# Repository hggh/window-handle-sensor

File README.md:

### window handle sensor

get the status of your windows. sensor is between your handle and the window.

### TODO

 * replace xc6220 footprint with the one from KiCAD
 * add a button for wifi reset
 * battery connector rotate it: open should be on top

### PCBs

this project contains of two pcbs.

#### window-handle-sensor

This PCB is the sensor. It has three hall sensors placed on a **0.6mm** pcb.

library used: https://github.com/hggh/kicad-libraries

##### BOM of window-handle-sensor pcb

| number | name |
|---| ---|
| C1,C2,C3 | ceramic cap 0.1 µF SMD 0805 |
| U1,U2,U3 | Infineon TLE4913 |

#### ESP controller board

This PCB is the controller board with the ESP32-S2. The thickness of this pcb can be 1.0-1.6mm.

##### BOM of esp32-s2 pcb

| number | name |
|--- | ---|
| C1 | ceramic cap 22µF SMD 0805 |
| C2 | ceramic cap 4.7µF SMD 0805 |
| C3 | tantalum cap 220µF SMD EIA-7343-31 |
| C4 | ceramic cap 100nF SMD 0805 |
| C5 | ceramic cap 1µF SMD 0805 |
| U1 | XC6220 3.0V SOT-25 |
| U2 | ESP32-S2-WROOM |
| H1 | 2.54mm 2x3 pin header |
| J1 | JST PH S2B-PH-K |
| Q1 | BC817 |
| Q2 | BC807 |
| R1, R14 | 10k SMD0805 |
| R2, R3, R4 | 100 SMD0805 |
| R5, R6, R7, R8, R9 | 10M SMD 0805 |
| R10, R11 | 1k1 SMD 0805 |
| R12, R13 | 10k SMD 0805 |

### case

The inlay is placed on the square bolt with 3x magnets.

Magnets: Ø 2 mm, h=1mm (strength: 110g): https://www.supermagnete.de/eng/disc-magnets-neodymium/disc-magnet-2mm-1mm_S-02-01-N

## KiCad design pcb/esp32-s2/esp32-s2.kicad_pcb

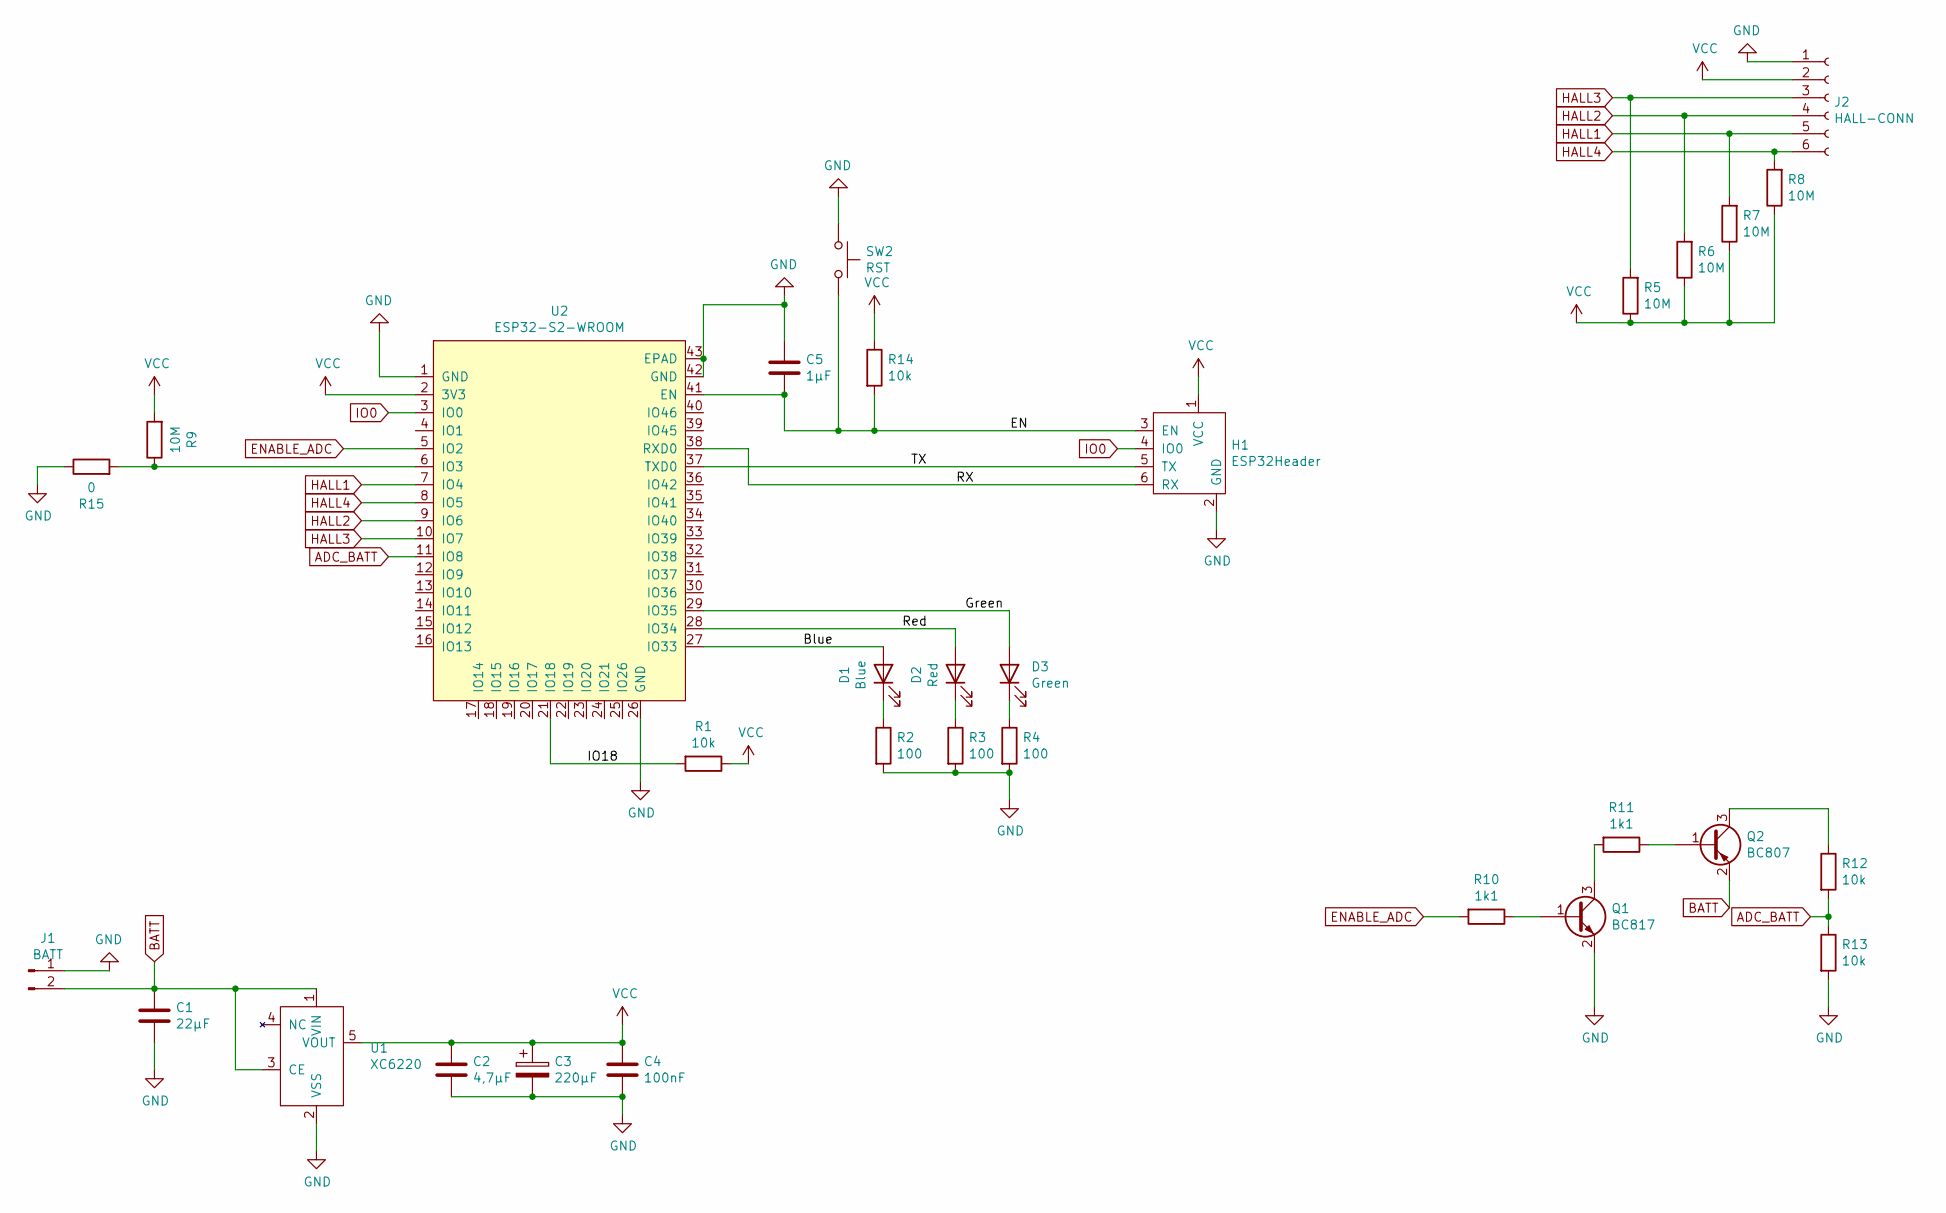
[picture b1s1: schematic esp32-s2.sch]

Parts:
C1: 22µF; C_0805_2012Metric
C2: 4,7µF; C_0805_2012Metric
C3: 220µF; CP_EIA-7343-31_Kemet-D
C4: 100nF; C_0805_2012Metric
C5: 1µF; C_0805_2012Metric
D1: Blue; LED_0805_2012Metric
D2: Red; LED_0805_2012Metric
D3: Green; LED_0805_2012Metric
H1: ESP32Header; esp32-prog-header
J1: BATT; JST_PH_S2B-PH-K_1x02_P2.00mm_Horizontal
J2: HALL-CONN; PinHeader_1x06_P2.00mm_Vertical
Q1: BC817; SOT-23
Q2: BC807; SOT-23
R1, R12, R13: 10k; R_0805_2012Metric
R2, R3, R4: 100; R_0805_2012Metric
R5, R6, R7, R8, R9: 10M; R_0805_2012Metric
R10, R11: 1k1; R_0805_2012Metric
R14: 10k; C_0805_2012Metric
R15: 0; R_0805_2012Metric
SW2: RST; SMD_Button
U1: XC6220
U2: ESP32-S2-WROOM

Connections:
/Blue: D1.2 (A), U2.27 (IO33)
/EN: C5.2, H1.3 (EN), R14.2, SW2.2, U2.41 (EN)
/Green: D3.2 (A), U2.29 (IO35)
/IO18: R1.2, U2.21 (IO18)
/RX: H1.6 (RX), U2.38 (RXD0)
/Red: D2.2 (A), U2.28 (IO34)
/TX: H1.5 (TX), U2.37 (TXD0)
ADC_BATT: R12.2, R13.1, U2.11 (IO8)
BATT: C1.1, J1.2, Q2.2 (E), U1.1 (VIN), U1.3 (CE)
ENABLE_ADC: R10.2, U2.5 (IO2)
GND: C1.2, C2.2, C3.2, C4.2, C5.1, H1.2 (GND), J1.1, J2.1, Q1.2 (E), R2.2, R3.2, R4.2, R13.2, R15.1, SW2.1, U1.2 (VSS), U2.1 (GND), U2.26 (GND), U2.42 (GND), U2.43 (EPAD)
HALL1: J2.5, R7.2, U2.7 (IO4)
HALL2: J2.4, R6.2, U2.9 (IO6)
HALL3: J2.3, R5.2, U2.10 (IO7)
HALL4: J2.6, R8.2, U2.8 (IO5)
IO0: H1.4 (IO0), U2.3 (IO0)
unnamed: D1.1 (K), R2.1
unnamed: D2.1 (K), R3.1
unnamed: D3.1 (K), R4.1
unnamed: Q1.1 (B), R10.1
unnamed: Q1.3 (C), R11.2
unnamed: Q2.1 (B), R11.1
unnamed: Q2.3 (C), R12.1
unnamed: R9.1, R15.2, U2.6 (IO3)
VCC: C2.1, C3.1, C4.1, H1.1 (VCC), J2.2, R1.1, R5.1, R6.1, R7.1, R8.1, R9.2, R14.1, U1.5 (VOUT), U2.2 (3V3)

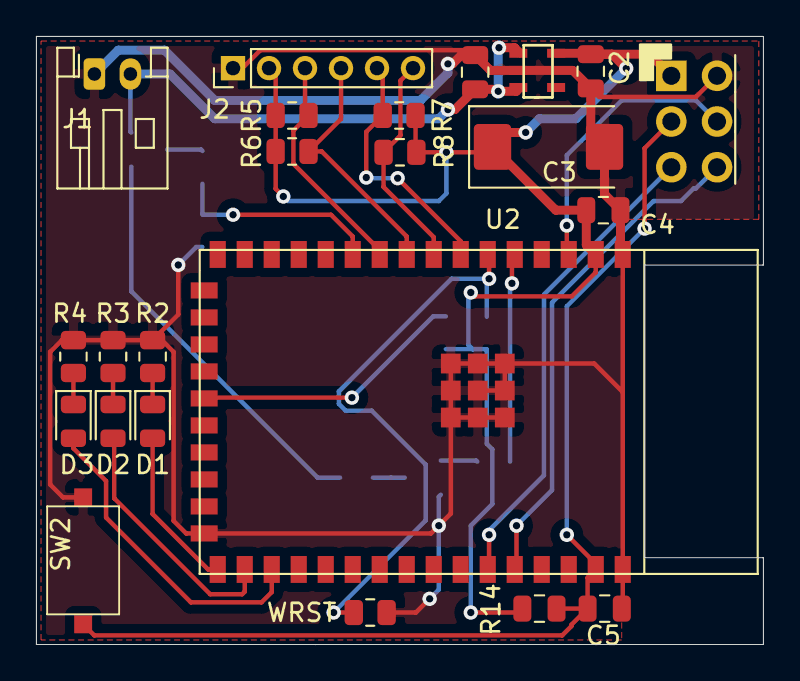
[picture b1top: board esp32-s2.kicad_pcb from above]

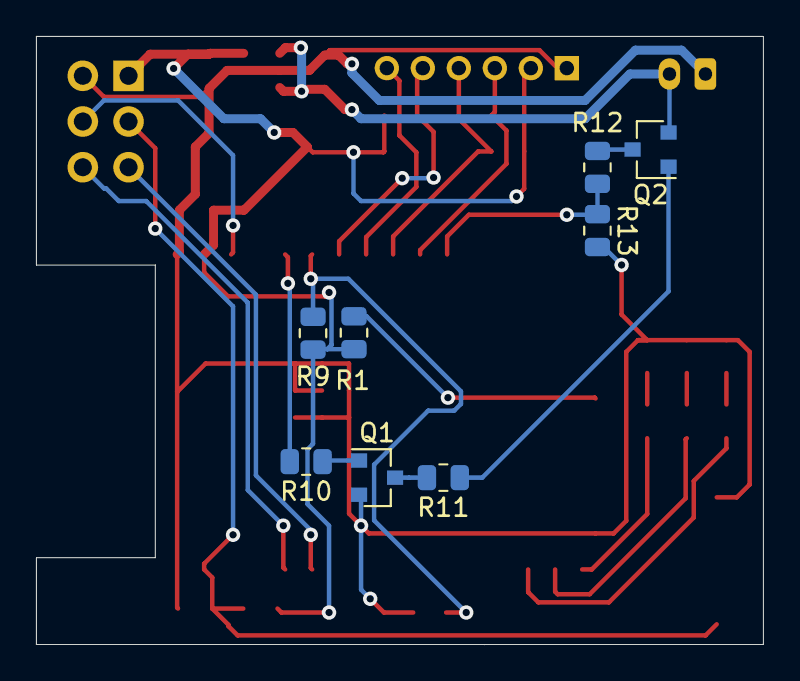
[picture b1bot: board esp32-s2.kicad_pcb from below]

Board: 2 copper layers, 40.4 x 33.8 mm, 31 parts (8 on the bottom side), 25 nets.

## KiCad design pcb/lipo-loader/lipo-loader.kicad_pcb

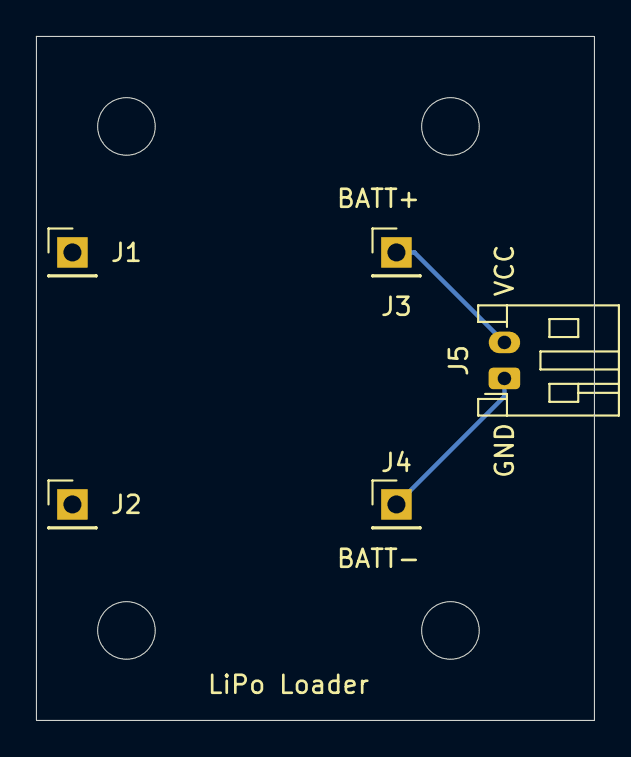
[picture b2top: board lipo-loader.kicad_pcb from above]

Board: 2 copper layers, 31.0 x 38.0 mm, 9 parts (0 on the bottom side), 2 nets.

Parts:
H1, H2, H3, H4: M; MountingHole_3.2mm_M3
J1: IN_VCC; PinHeader_1x01_P2.54mm_Vertical
J2: IN_GND; PinHeader_1x01_P2.54mm_Vertical
J3: TP_BATT_VCC; PinHeader_1x01_P2.54mm_Vertical
J4: TP_BATT_GND; PinHeader_1x01_P2.54mm_Vertical
J5: BATT; JST_PH_S2B-PH-K_1x02_P2.00mm_Horizontal

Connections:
/GND: J4.1, J5.1
/VCC: J3.1, J5.2

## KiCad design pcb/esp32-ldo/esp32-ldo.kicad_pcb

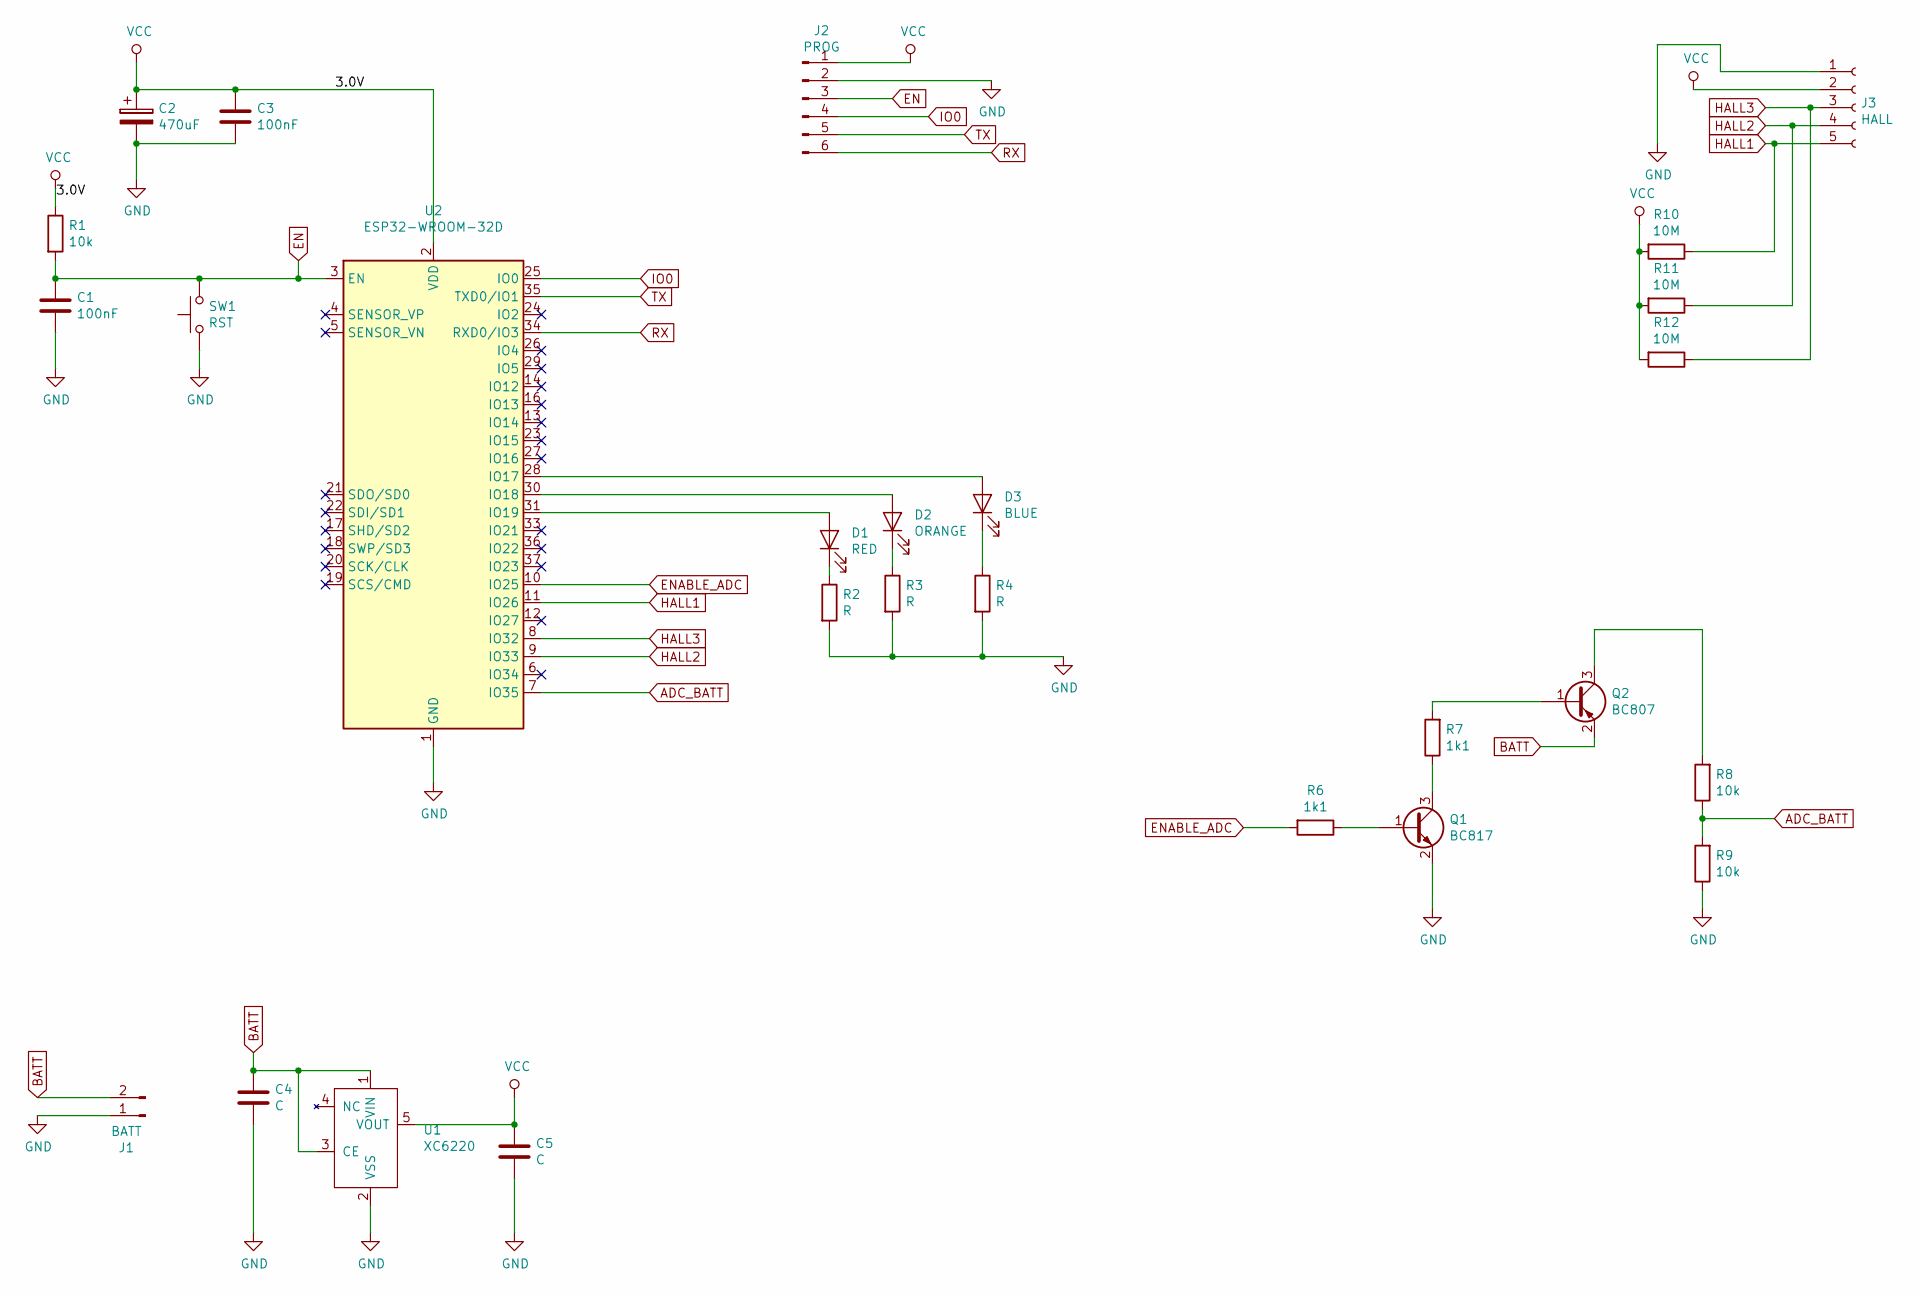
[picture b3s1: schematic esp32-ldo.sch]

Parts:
C1, C3: 100nF; C_0805_2012Metric
C2: 470uF; CP_EIA-7360-38_Kemet-E
C4, C5: C; C_0805_2012Metric
D1: RED; LED_0805_2012Metric
D2: ORANGE; LED_0805_2012Metric
D3: BLUE; LED_0805_2012Metric
J1: BATT; JST_PH_S2B-PH-K_1x02_P2.00mm_Horizontal
J2: PROG; PinHeader_2x03_P2.54mm_Vertical
J3: HALL; PinHeader_1x05_P2.00mm_Vertical
Q1: BC817; SOT-23
Q2: BC807; SOT-23
R1, R8, R9: 10k; R_0805_2012Metric
R2, R3, R4: R; R_0805_2012Metric
R6, R7: 1k1; R_0805_2012Metric
R10, R11, R12: 10M; R_0805_2012Metric
SW1: RST; SMD_Button
U1: XC6220
U2: ESP32-WROOM-32D; ESP32-WROOM-32

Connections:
ADC_BATT: R8.1, R9.2, U2.7 (IO35)
BATT: C4.1, J1.2, Q2.2 (E), U1.1 (VIN), U1.3 (CE)
EN: C1.1, J2.3, R1.2, SW1.2, U2.3 (EN)
ENABLE_ADC: R6.2, U2.10 (IO25)
GND: C1.2, C2.2, C3.2, C4.2, C5.2, J1.1, J2.2, J3.1, Q1.2 (E), R2.2, R3.2, R4.2, R9.1, SW1.1, U1.2 (VSS), U2.1 (GND), U2.15 (GND), U2.38 (GND)
HALL1: J3.5, R10.1, U2.11 (IO26)
HALL2: J3.4, R11.1, U2.9 (IO33)
HALL3: J3.3, R12.1, U2.8 (IO32)
IO0: J2.4, U2.25 (IO0)
unnamed: D1.1 (K), R2.1
unnamed: D1.2 (A), U2.31 (IO19)
unnamed: D2.1 (K), R3.1
unnamed: D2.2 (A), U2.30 (IO18)
unnamed: D3.1 (K), R4.1
unnamed: D3.2 (A), U2.28 (IO17)
unnamed: Q1.1 (B), R6.1
unnamed: Q1.3 (C), R7.1
unnamed: Q2.1 (B), R7.2
unnamed: Q2.3 (C), R8.2
RX: J2.6, U2.34 (RXD0/IO3)
TX: J2.5, U2.35 (TXD0/IO1)
VCC: C2.1, C3.1, C5.1, J2.1, J3.2, R1.1, R10.2, R11.2, R12.2, U1.5 (VOUT), U2.2 (VDD)

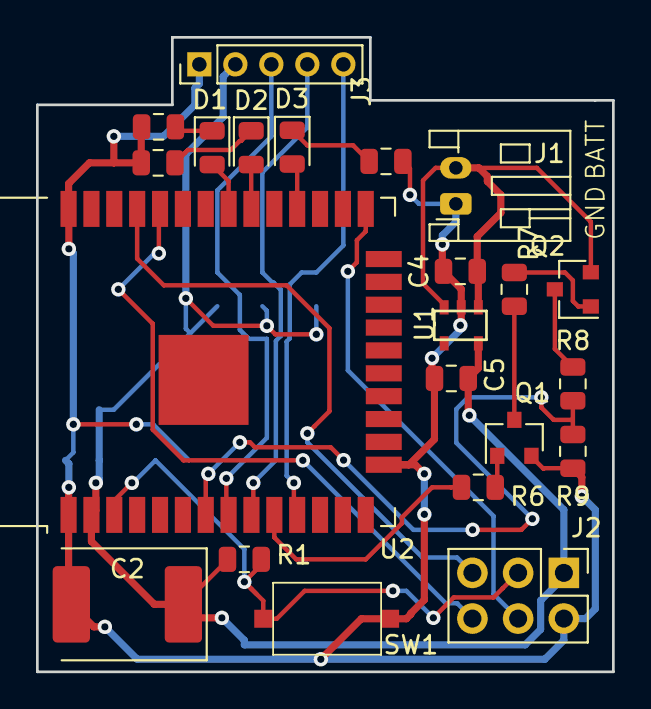
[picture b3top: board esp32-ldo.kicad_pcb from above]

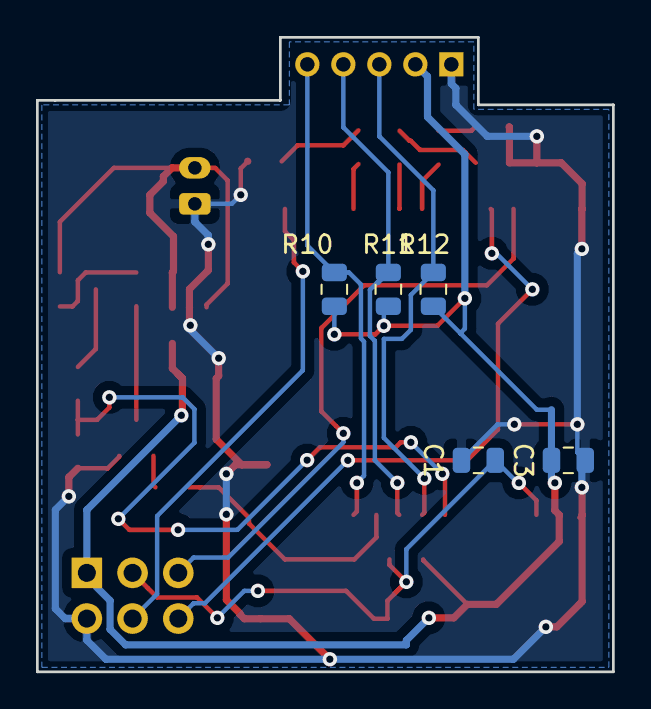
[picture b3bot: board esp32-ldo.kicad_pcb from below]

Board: 2 copper layers, 32.0 x 35.2 mm, 27 parts (5 on the bottom side), 22 nets.

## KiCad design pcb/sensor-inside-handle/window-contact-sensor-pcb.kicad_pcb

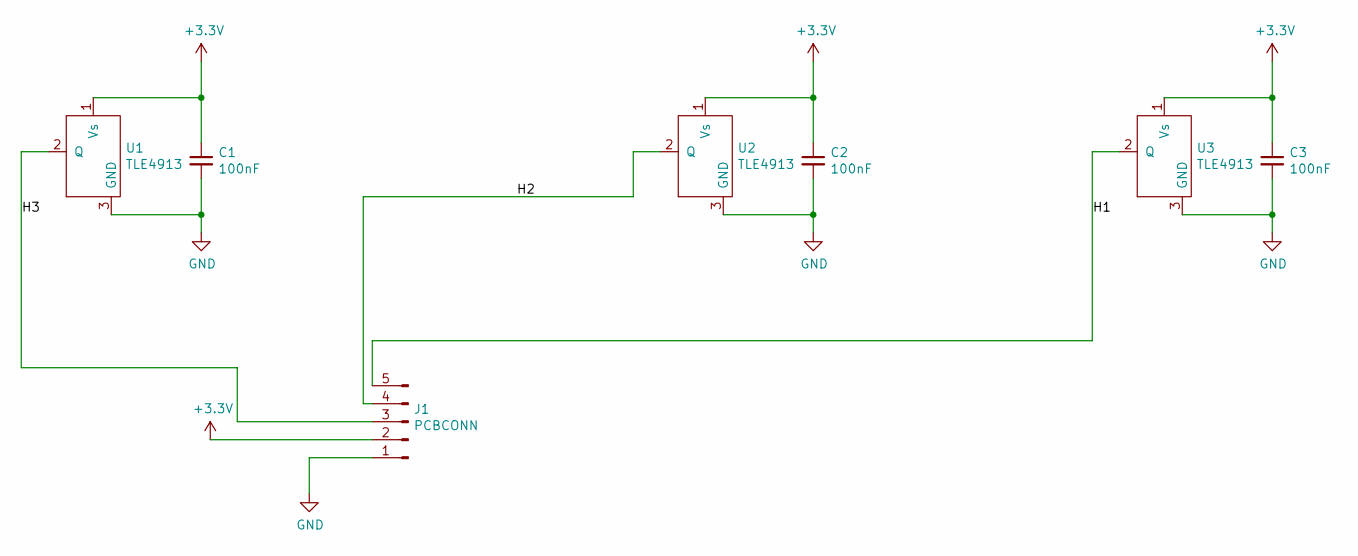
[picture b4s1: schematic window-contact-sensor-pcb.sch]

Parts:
C1, C2, C3: 100nF; C_0805_2012Metric
J1: PCBCONN; PinHeader_1x05_P2.00mm_Vertical
U1, U2, U3: TLE4913; SC-59

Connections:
+3V3: C1.1, C2.1, C3.1, J1.2, U1.1 (Vs), U2.1 (Vs), U3.1 (Vs)
/H1: J1.5, U3.2 (Q)
/H2: J1.4, U2.2 (Q)
/H3: J1.3, U1.2 (Q)
GND: C1.2, C2.2, C3.2, J1.1, U1.3 (GND), U2.3 (GND), U3.3 (GND)

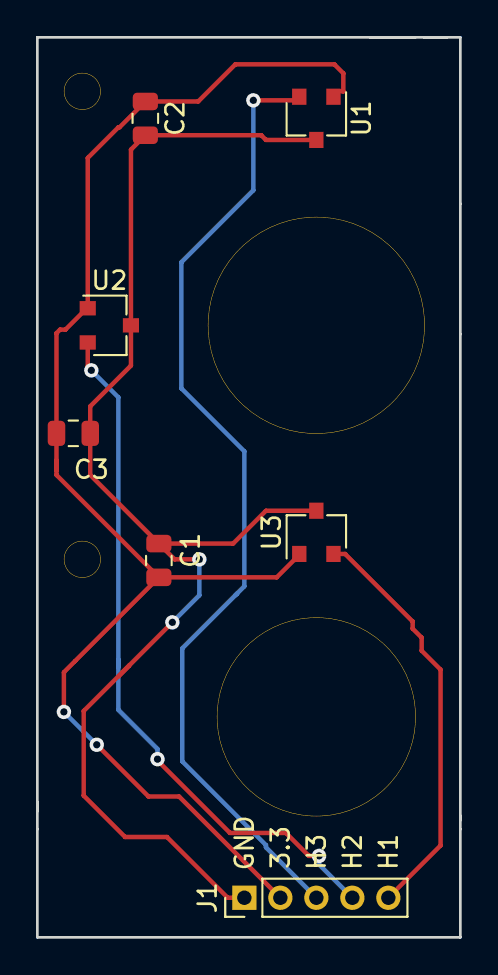
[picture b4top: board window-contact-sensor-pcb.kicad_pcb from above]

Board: 2 copper layers, 23.5 x 50.0 mm, 7 parts (0 on the bottom side), 5 nets.

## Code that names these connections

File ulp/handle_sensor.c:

#include <stdio.h>
#include <stdint.h>
#include <stdbool.h>
#include "ulp_riscv/ulp_riscv.h"
#include "ulp_riscv/ulp_riscv_utils.h"

#define HALL1_GPIO 4
#define HALL2_GPIO 5
#define HALL3_GPIO 6
#define HALL4_GPIO 7

uint8_t hall1_status_cur;
uint8_t hall2_status_cur;
uint8_t hall3_status_cur;

uint8_t hall1_status;
uint8_t hall2_status;
uint8_t hall3_status;

static inline uint8_t gpio_get_level(uint8_t gpio_num) {
  return (uint8_t)((REG_GET_FIELD(RTC_GPIO_IN_REG, RTC_GPIO_IN_NEXT) & BIT(gpio_num)) ? 1 : 0);
}

int main (void) {
  hall1_status_cur = gpio_get_level(HALL1_GPIO);
  if (hall1_status_cur != hall1_status) {
    hall1_status = hall1_status_cur;
    ulp_riscv_wakeup_main_processor();
  }

  hall2_status_cur = gpio_get_level(HALL2_GPIO);
  if (hall2_status_cur != hall2_status) {
    hall2_status = hall2_status_cur;
    ulp_riscv_wakeup_main_processor();
  }

  hall3_status_cur = gpio_get_level(HALL3_GPIO);
  if (hall3_status_cur != hall3_status) {
    hall3_status = hall3_status_cur;
    ulp_riscv_wakeup_main_processor();
  }

  return 0;
}

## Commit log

2020-07-18 initial commit of sensor pcb with inlay
2020-08-02 initial commit; current 10-12 µA in deep sleep
2020-08-02 disable BT
2020-08-02 cleanup
2020-08-02 wifi connect with timeout
2020-08-02 first mqtt qos = 2 send test without any timeout
2020-08-07 add esp32 with ldo
2020-08-07 update pcb size
2020-08-07 update pcb: rst button
2020-08-07 fix edge cuts
2020-08-07 update final pcb
2020-08-12 wakeup by timer add adc base function
2020-08-12 exclude sdkconfig.old from run -t menuconfig
2020-08-13 send battery status, monitor mqtt send
2020-08-13 add openhab2 examples for mqtt and trigger low battery value
2020-08-14 rename topic
2020-08-14 use correct color code to display state
2020-08-14 light d3,d4 is no state is detected
2020-08-14 isolate pin before deep sleep. 70µA less
2020-08-18 OpenHab2: add rule to check if sensor was active last 25hours
2020-09-09 add port
2020-09-09 migrate to esp_netif from tcpip
2020-09-09 add todo
2020-09-26 Revert "migrate to esp_netif from tcpip"
    This reverts commit e737d5c4e92303c864b6b653a1da411fec993e34.
2020-09-26 use only 3 LEDs for Status green = position known, bloue = position unkown; red = send error
2020-09-26 add beta version pics
2020-09-26 pcb: removed LED 4
2020-09-27 add stl
2020-09-29 add sleep time start
2021-01-08 work on ESP32-S2
2021-01-09 update pcb for esp32s2
2021-01-15 working on ESP32-S2 support
2021-01-16 update pcb: add cap values
2021-01-18 remove ULP, use wakeup EXT0; use idf@master branch
2021-01-18 ESP32-S2 is now working, only ADC does not work yet
2021-01-18 disable wifi and adc on lightsleep
2021-01-18 add lipo loader with tp4056 pcb without protection ICs
2021-01-19 add bootcount, send it via mqtt, retry if sending error
2021-01-21 add boot count of ESP32s2 into openhab, to see if we have resets
2021-01-21 Final Update of LiPO Loader for the sensor
2021-01-25 update lipo loader
2021-02-05 add ADC to query battery voltage
2021-02-07 update footprint for XC6220
2021-02-12 update case
2021-02-15 add bom of esp32-s2
2021-02-15 updates case; splitted into two parts
2021-02-17 add lid
2021-02-19 updated pics
2021-05-15 'case' for loader
2021-10-03 moved to Arduino framework
2021-10-04 light red if no position of handle
2023-04-30 update pics
